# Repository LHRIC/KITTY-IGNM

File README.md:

# 4-Cylinder Ignition Module PCB

This is a custom PCB ignition module for a 4-cylinder engine.

The board uses four IGBTs as low-side switches, with one IGBT for each ignition coil signal.

## What It Does

- Takes in 4 ignition signals
- Uses each signal to control one IGBT
- Each IGBT connects one coil to ground when active
- Designed for low-side ignition coil switching

## Power Distribution

The board also has a simple 12V splice section.

It takes:

- 2 × 12V inputs

And provides:

- 4 × 12V outputs

The 12V traces are only used to split power to the coils. They are not used anywhere else on the board.

## Notes

- Made for a 4-cylinder ignition setup
- Low-side switched design
- 12V section is only for coil power distribution
- Coil dwell/control timing should come from the ECU

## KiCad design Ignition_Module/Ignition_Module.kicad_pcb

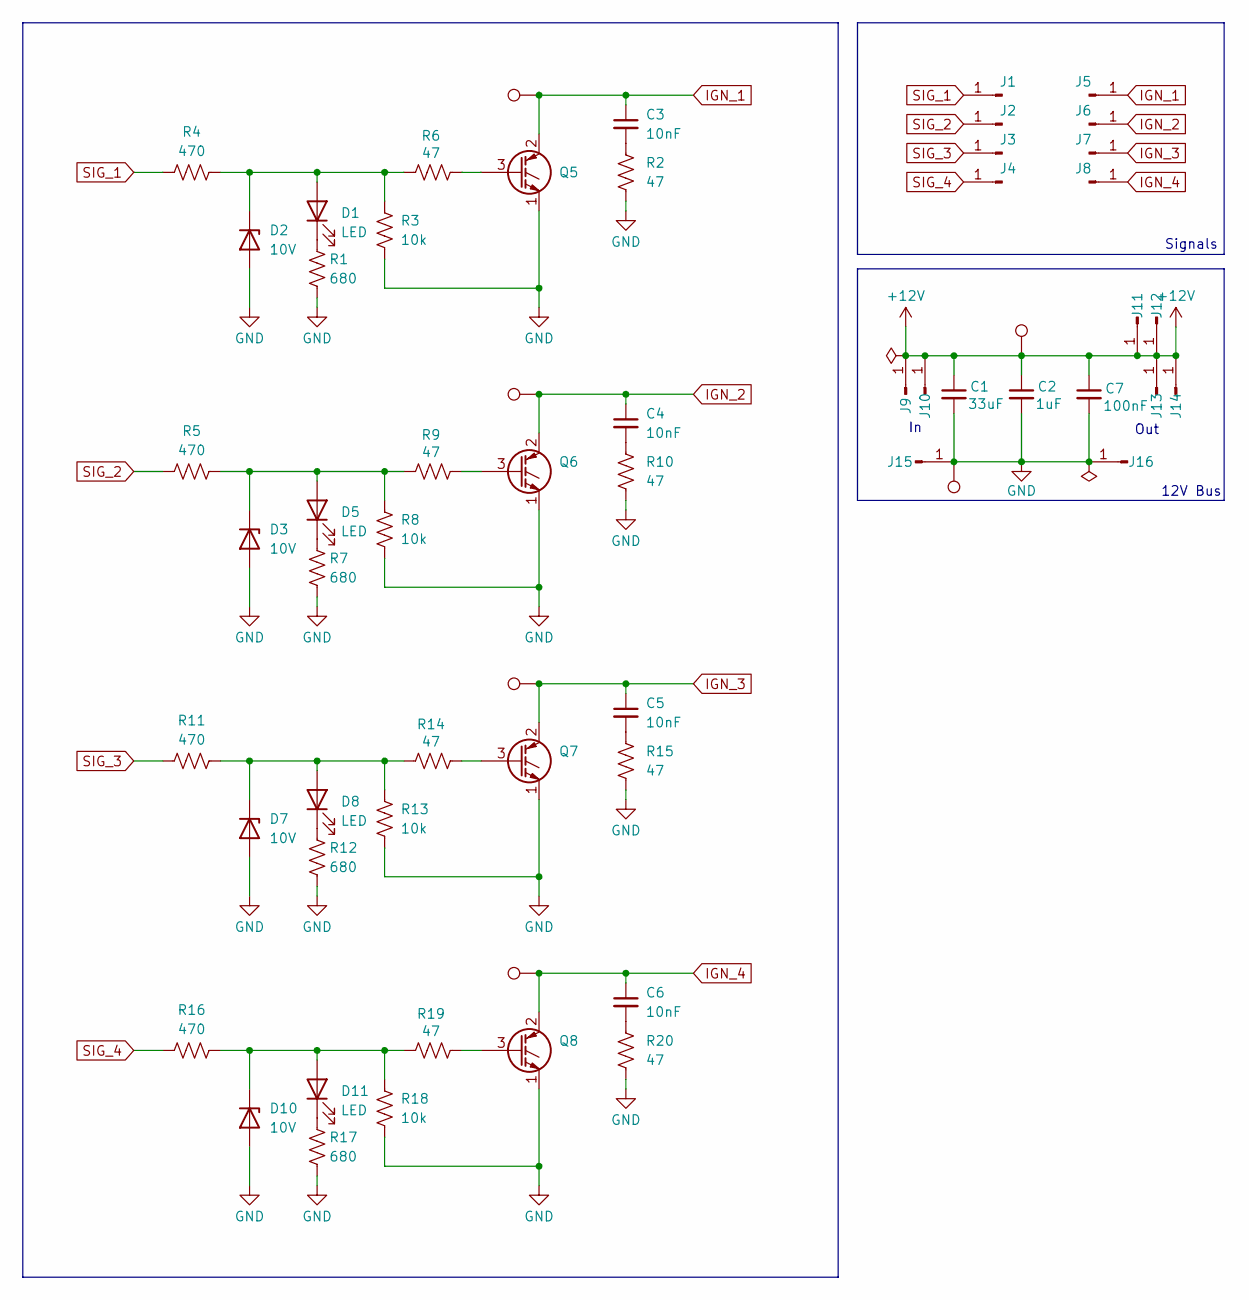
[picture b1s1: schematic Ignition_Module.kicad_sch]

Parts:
C1: 33uF; C_0805_2012Metric_Pad1.18x1.45mm_HandSolder
C2: 1uF; C_0603_1608Metric_Pad1.08x0.95mm_HandSolder
C3, C4, C5, C6: 10nF; C_0603_1608Metric_Pad1.08x0.95mm_HandSolder
C7: 100nF; C_0603_1608Metric_Pad1.08x0.95mm_HandSolder
D1, D5, D8, D11: LED; LED_0603_1608Metric_Pad1.05x0.95mm_HandSolder
D2, D3, D7, D10: 10V; D_SOD-523
J1, J2, J3, J4, J5, J6, J7, J8, J9, J10, J11, J12, J13, J14, J15, J16: Conn_01x01_Pin; SolderWire-1sqmm_1x01_D1.4mm_OD3.9mm
Q5, Q6, Q7, Q8: Q_NIGBT_ECG; TO-263-2
R1, R7, R12, R17: 680; R_0603_1608Metric_Pad0.98x0.95mm_HandSolder
R2, R6, R9, R10, R14, R15, R19, R20: 47; R_0603_1608Metric_Pad0.98x0.95mm_HandSolder
R3, R8, R13, R18: 10k; R_0603_1608Metric_Pad0.98x0.95mm_HandSolder
R4, R5, R11, R16: 470; R_0603_1608Metric_Pad0.98x0.95mm_HandSolder
TP1, TP2, TP3, TP4, TP5, TP6: TestPoint; TestPoint_Keystone_5000-5004_Miniature

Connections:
+12V: C1.1, C2.1, C7.1, J9.1, J10.1, J11.1, J12.1, J13.1, J14.1, TP2.1
GND: C1.2, C2.2, C7.2, D2.2 (A), D3.2 (A), D7.2 (A), D10.2 (A), J15.1, J16.1, Q5.1 (E), Q6.1 (E), Q7.1 (E), Q8.1 (E), R1.2, R2.2, R3.2, R7.2, R8.2, R10.2, R12.2, R13.2, R15.2, R17.2, R18.2, R20.2, TP1.1
IGN_1: C3.1, J5.1, Q5.2 (C), TP5.1
IGN_2: C4.1, J6.1, Q6.2 (C), TP4.1
IGN_3: C5.1, J7.1, Q7.2 (C), TP3.1
IGN_4: C6.1, J8.1, Q8.2 (C), TP6.1
unnamed: C3.2, R2.1
unnamed: C4.2, R10.1
unnamed: C5.2, R15.1
unnamed: C6.2, R20.1
unnamed: D1.2 (A), D2.1 (K), R3.1, R4.2, R6.1
unnamed: D1.1 (K), R1.1
unnamed: D3.1 (K), D5.2 (A), R5.2, R8.1, R9.1
unnamed: D5.1 (K), R7.1
unnamed: D7.1 (K), D8.2 (A), R11.2, R13.1, R14.1
unnamed: D8.1 (K), R12.1
unnamed: D10.1 (K), D11.2 (A), R16.2, R18.1, R19.1
unnamed: D11.1 (K), R17.1
unnamed: Q5.3 (G), R6.2
unnamed: Q6.3 (G), R9.2
unnamed: Q7.3 (G), R14.2
unnamed: Q8.3 (G), R19.2
SIG_1: J1.1, R4.1
SIG_2: J2.1, R5.1
SIG_3: J3.1, R11.1
SIG_4: J4.1, R16.1

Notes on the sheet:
Out
Signals
12V Bus

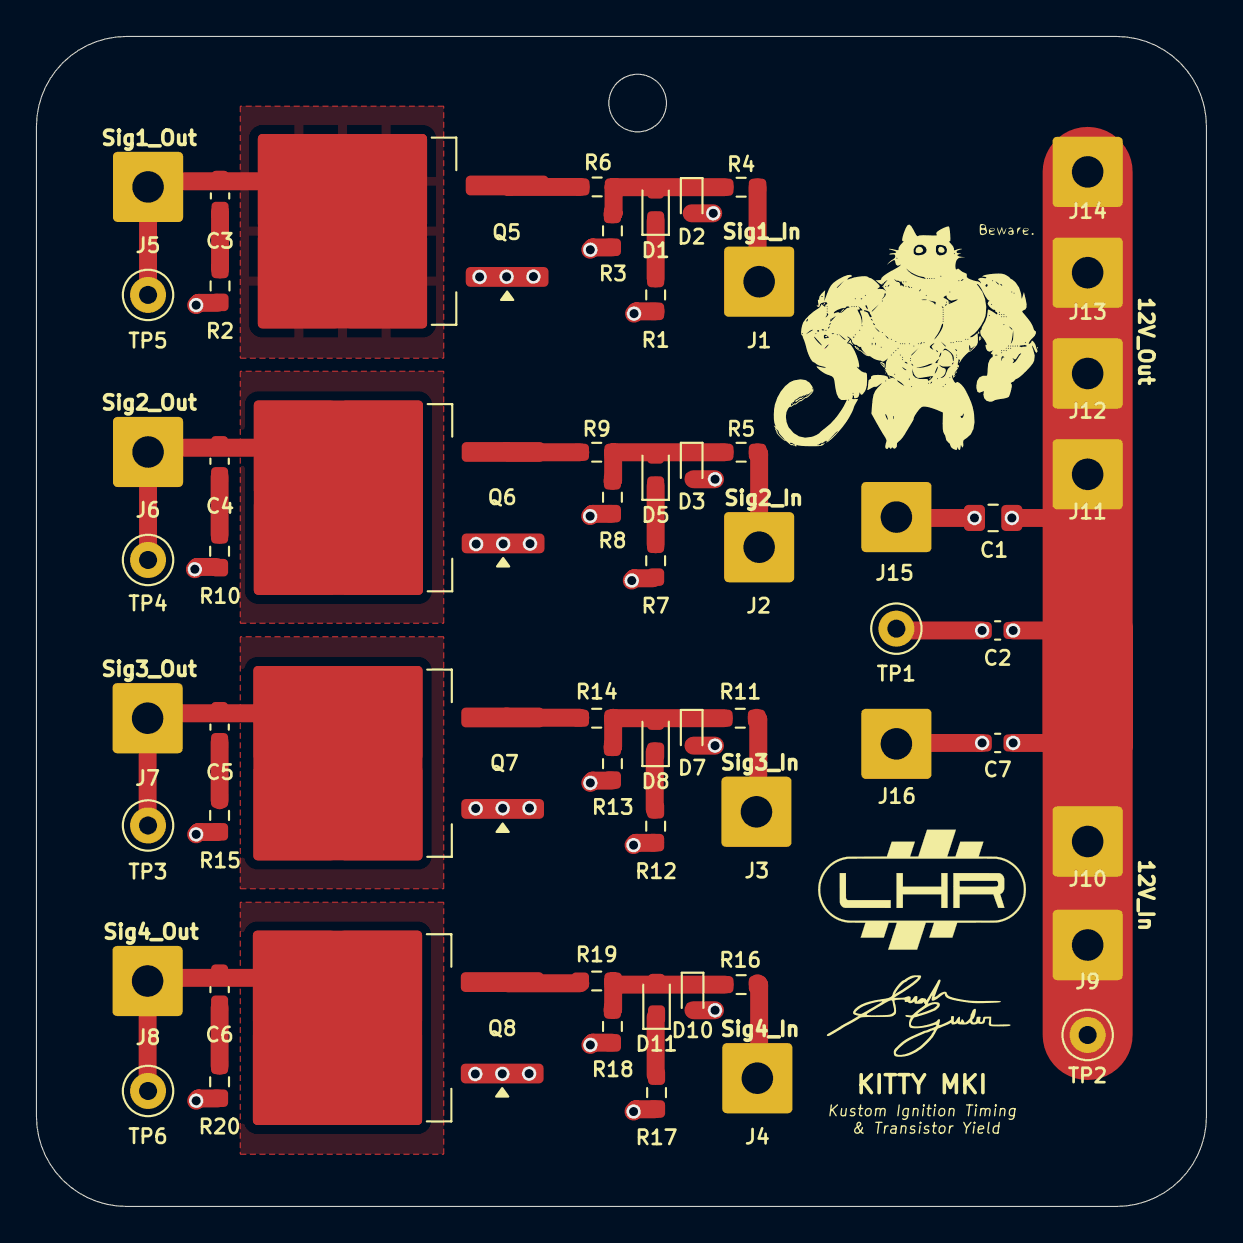
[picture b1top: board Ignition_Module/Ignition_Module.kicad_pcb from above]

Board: 2 copper layers, 65.0 x 65.0 mm, 61 parts (0 on the bottom side), 26 nets.

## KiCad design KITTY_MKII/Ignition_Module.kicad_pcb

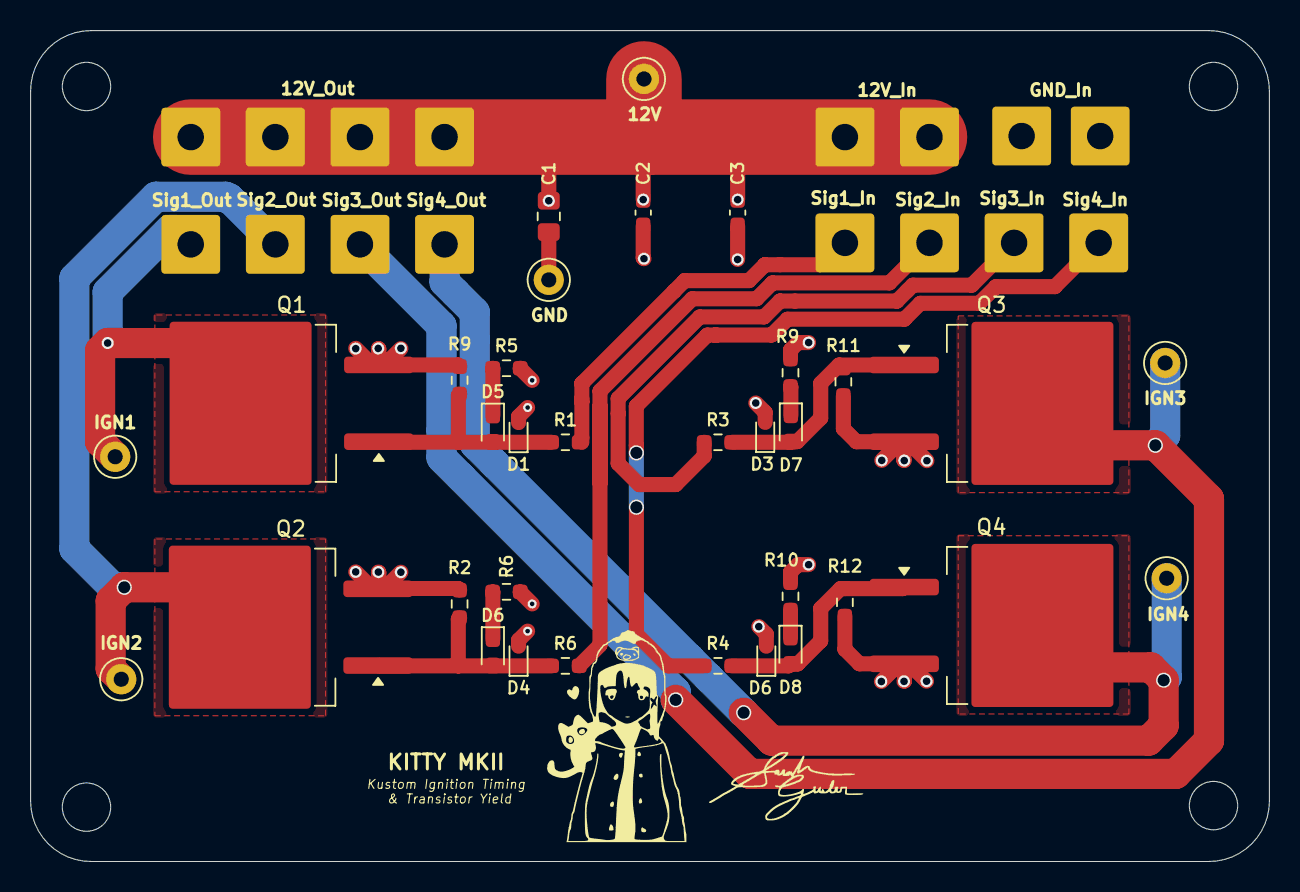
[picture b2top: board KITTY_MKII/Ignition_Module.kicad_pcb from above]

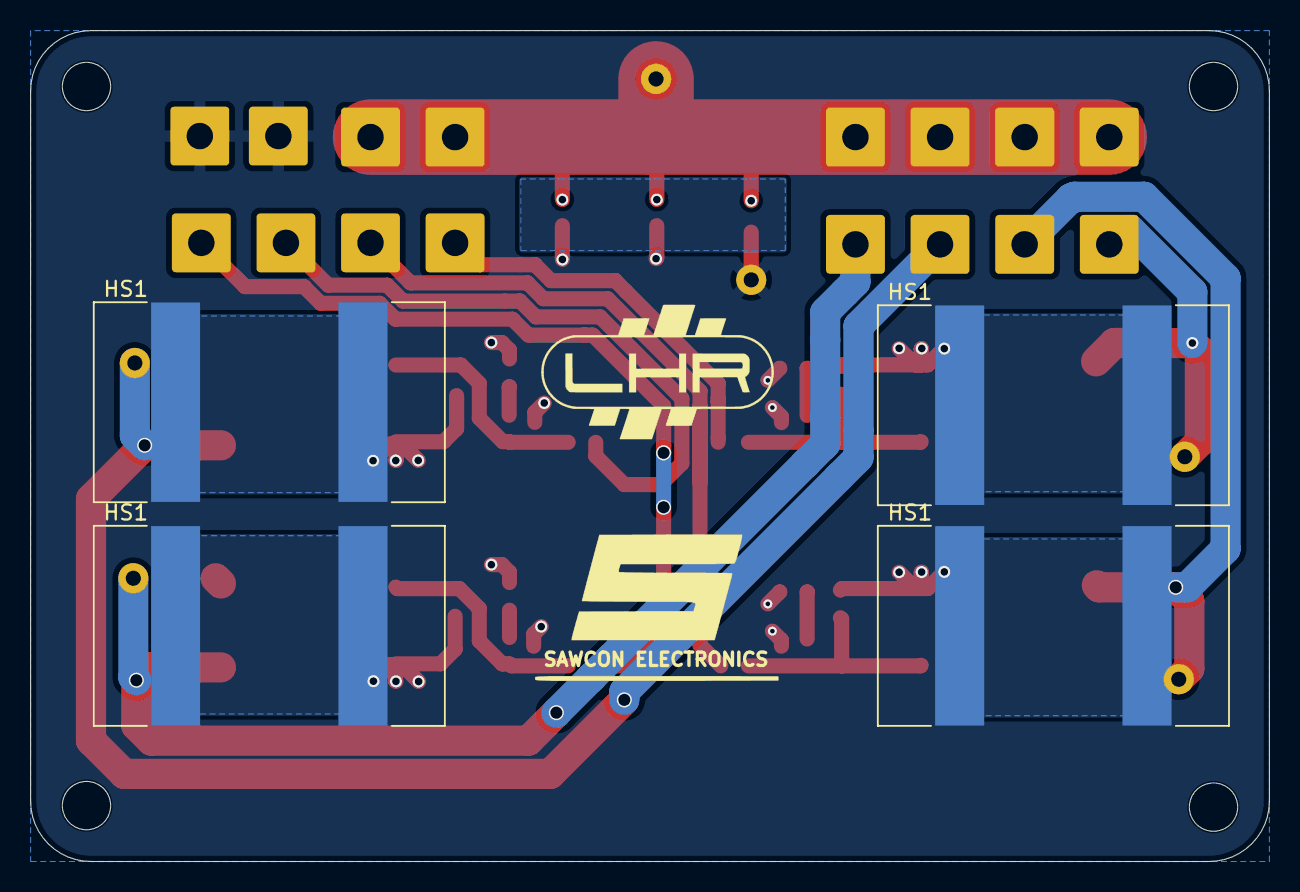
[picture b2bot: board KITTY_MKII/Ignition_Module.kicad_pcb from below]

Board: 2 copper layers, 82.0 x 55.0 mm, 53 parts (4 on the bottom side), 17 nets.

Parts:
C1: 33uF; C_0805_2012Metric_Pad1.18x1.45mm_HandSolder
C2: 1uF; C_0603_1608Metric_Pad1.08x0.95mm_HandSolder
C3: 100nF; C_0603_1608Metric_Pad1.08x0.95mm_HandSolder
D1, D3, D4, D6: 10V; D_SOD-523
D5, D6#2, D7, D8: LED; LED_0603_1608Metric_Pad1.05x0.95mm_HandSolder
HS1, HS1#2, HS1#3, HS1#4: Heatsink; Heatsink_Fischer_FK24413DPAK_23x13mm
J1, J2, J3, J4, J5, J6, J7, J8, J9, J10, J11, J12, J13, J14, J15, J16: Conn_01x01_Pin; SolderWire-1sqmm_1x01_D1.4mm_OD3.9mm
Q1, Q2, Q3, Q4: Q_NIGBT_ECG; TO-263-2
R1, R3, R4, R6: 470; R_0603_1608Metric_Pad0.98x0.95mm_HandSolder
R2, R9#2, R11, R12: 10k; R_0603_1608Metric_Pad0.98x0.95mm_HandSolder
R5, R6#2, R9, R10: 680; R_0603_1608Metric_Pad0.98x0.95mm_HandSolder
TP1, TP2, TP3, TP4, TP5, TP6: TestPoint; TestPoint_Keystone_5000-5004_Miniature

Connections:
+12V: C1.1, C2.1, C3.1, J1.1 (Pin_1_1), J3.1 (Pin_1_1), J13.1 (Pin_1_1), J14.1 (Pin_1_1), J15.1 (Pin_1_1), J16.1 (Pin_1_1), TP6.1 (1_1)
/Net-(D5-K): D6#2.1 (K), R6#2.1
/Net-(D7-K): D3.1 (K), D7.2 (A), R3.2, R11.1
GND: C1.2, C2.2, C3.2, D1.2 (A), D3.2 (A), D4.2 (A), D6.2 (A), J2.1 (Pin_1_1), J12.1 (Pin_1_1), Q1.3 (E), Q2.3 (E), Q3.3 (E), Q4.3 (E), R2.2, R5.2, R6#2.2, R9.2, R9#2.2, R10.2, R11.2, R12.2, TP5.1 (1_1)
IGN_1: J8.1 (Pin_1_1), Q1.2 (C), TP1.1 (1_1)
IGN_2: J9.1 (Pin_1_1), Q2.2 (C), TP2.1 (1_1)
IGN_3: J10.1 (Pin_1_1), Q3.2 (C), TP3.1 (1_1)
IGN_4: J11.1 (Pin_1_1), Q4.2 (C), TP4.1 (1_1)
unnamed: D1.1 (K), D5.2 (A), R1.2, R9#2.1
unnamed: D4.1 (K), Q2.1 (G), R2.1, R6.2
unnamed: D8.2 (A), R4.2, R12.1
unnamed: D5.1 (K), R5.1
unnamed: D6.1 (K), Q4.1 (G)
SIG_1: J4.1 (Pin_1_1), R1.1
SIG_2: J5.1 (Pin_1_1), R6.1
SIG_3: J6.1 (Pin_1_1), R3.1
SIG_4: J7.1 (Pin_1_1), R4.1

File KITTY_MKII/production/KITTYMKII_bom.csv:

Designator,Footprint,Quantity,Value,LCSC Part #
C1,0805,1,33uF,
C2,0603,1,1uF,
C3,0603,1,100nF,
"D1, D2, D7, D8",0603,4,LED,
"D3, D4, D5, D6",D_SOD-523,4,10V,
"J1, J10, J11, J12, J13, J14, J15, J16, J2, J3, J4, J5, J6, J7, J8, J9",SolderWire-1sqmm_1x01_D1.4mm_OD3.9mm,16,Conn_01x01_Pin,
"Q1, Q2, Q3, Q4",TO-263-2,4,Q_NIGBT_ECG,
"R1, R11, R12, R2",0603,4,10k,
"R10, R3, R4, R9",0603,4,680,
"R5, R6, R7, R8",0603,4,470,
"TP1, TP2, TP3, TP4, TP5, TP6",TestPoint_Keystone_5000-5004_Miniature,6,TestPoint,

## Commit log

2026-02-13 all the stuff
2026-03-04 added mounting holes + silkscreen
2026-03-04 removed diode - makes gate float 10V
2026-03-14 Added name and year
2026-04-03 MKII, flipped footprint and rearranged.
2026-04-21 working on enclosure
2026-05-03 readme
2026-05-04 enclosure just needs latches/attachment points for the two halves
2026-05-10 enclosure rev2 done, added latches
